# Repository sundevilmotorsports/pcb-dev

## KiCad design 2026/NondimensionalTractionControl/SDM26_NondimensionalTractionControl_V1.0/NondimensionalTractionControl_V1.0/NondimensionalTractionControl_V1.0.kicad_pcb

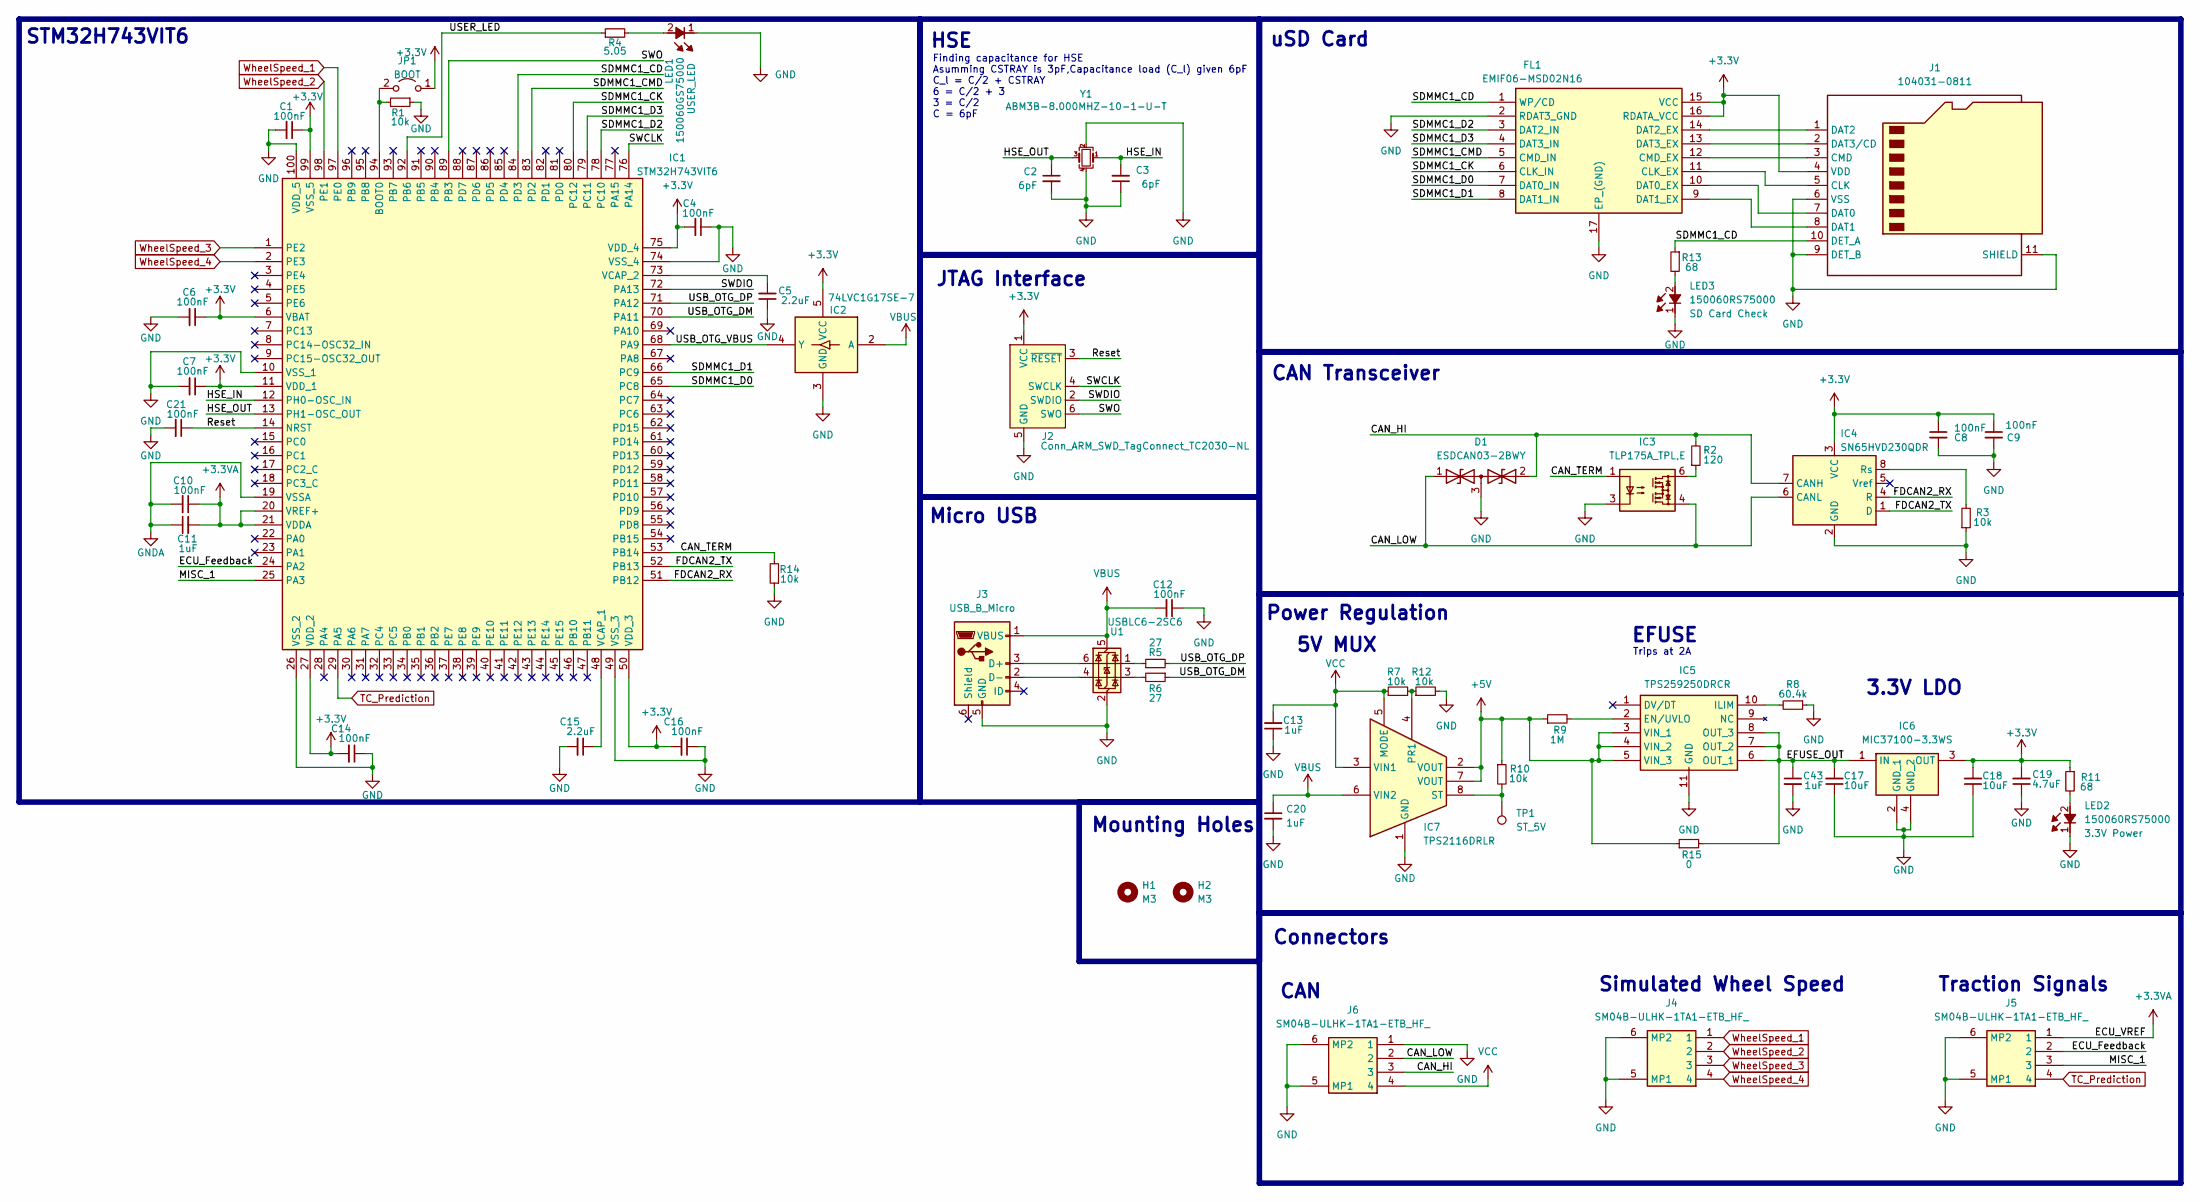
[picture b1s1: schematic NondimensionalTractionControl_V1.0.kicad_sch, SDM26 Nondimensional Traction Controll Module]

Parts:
C1, C4, C6, C7, C8, C9, C10, C12, C14, C16, C21: 100nF; C_0603_1608Metric
C2, C3: 6pF; C_0603_1608Metric
C5, C15: 2.2uF; C_0603_1608Metric
C11, C13, C20, C43: 1uF; C_0603_1608Metric
C17, C18: 10uF; C_0603_1608Metric
C19: 4.7uF; C_0603_1608Metric
D1: ESDCAN03-2BWY; SOT65P210X110-3N; Mouser Part Number 511-ESDCAN03-2BWY
FL1: EMIF06-MSD02N16; EMIF06MSD02N16; Mouser Part Number 511-EMIF06-MSD02N16
H1, H2: M3; MountingHole_3.2mm_M3
IC1: STM32H743VIT6; QFP50P1600X1600X160-100L; Mouser Part Number 511-STM32H743VIT6
IC2: 74LVC1G17SE-7; SOT65P210X110-5L; Mouser Part Number 621-74LVC1G17SE-7
IC3: TLP175A_TPL,E; TLP266J; Mouser Part Number 757-TLP175A(TPLE
IC4: SN65HVD230QDR; SOIC127P600X175-8L; Mouser Part Number 595-SN65HVD230QDR
IC5: TPS259250DRCR; SON50P300X300X100-11L-D; Mouser Part Number 595-TPS259250DRCR
IC6: MIC37100-3.3WS; SOT230P700X180-4N; Mouser Part Number 998-MIC37100-3.3WS
IC7: TPS2116DRLR; SOTFL50P160X60-8L; Mouser Part Number 595-TPS2116DRLR
J1: 104031-0811; 1040310811; Mouser Part Number 538-104031-0811
J2: Conn_ARM_SWD_TagConnect_TC2030-NL; Tag-Connect_TC2030-IDC-NL_2x03_P1.27mm_Vertical
J3: USB_B_Micro; USB_Micro-B_Molex-105017-0001
J4, J5, J6: SM04B-ULHK-1TA1-ETB_HF_; SM04BULHK1TA1ETBHF; Mouser Part Number 306-SM4BULH1TA1ETBHF
JP1: BOOT; PinHeader_1x02_P2.54mm_Vertical
LED1: 150060GS75000; LEDC1608X80N; Mouser Part Number 710-150060GS75000
LED2, LED3: 150060RS75000; LEDC1608X80N; Mouser Part Number 710-150060RS75000
R1, R3, R7, R10, R12, R14: 10k; R_0603_1608Metric
R2: 120; R_0603_1608Metric
R4: 5.05; R_0603_1608Metric
R5, R6: 27; R_0603_1608Metric
R8: 60.4k; R_0603_1608Metric
R9: 1M; R_0603_1608Metric
R11, R13: 68; R_0603_1608Metric
R15: 0; R_0603_1608Metric
TP1: ST_5V; TestPoint_Pad_1.5x1.5mm
U1: USBLC6-2SC6; SOT-23-6
Y1: ABM3B-8.000MHZ-10-1-U-T; ABM3B; Mouser Part Number 815-ABM3B8MHZ101UT

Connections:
+3.3V: C1.1, C4.2, C6.1, C7.1, C8.1, C9.1, C14.2, C16.2, C18.2, C19.2, FL1.15 (VCC), FL1.16 (RDATA_VCC), IC1.6 (VBAT), IC1.11 (VDD_1), IC1.27 (VDD_2), IC1.50 (VDD_3), IC1.75 (VDD_4), IC1.99 (VSS_5), IC2.5 (VCC), IC4.3 (VCC), IC6.3 (OUT), J1.4 (VDD), J2.1 (VCC), JP1.1 (A), R11.1
+3.3VA: C10.1, C11.2, IC1.20 (VREF+), IC1.21 (VDDA), J5.1
+5V: IC5.3 (VIN_1), IC5.4 (VIN_2), IC5.5 (VIN_3), IC7.2 (VOUT), IC7.7 (VOUT), R9.1, R10.1, R15.1
/CAN_HI: D1.2, IC4.7 (CANH), J6.3, R2.2
/CAN_LOW: D1.1, IC3.4, IC4.6 (CANL), J6.2
/CAN_TERM: IC1.53 (PB14), IC3.1, R14.2
/ECU_Feedback: IC1.24 (PA2), J5.2
/EFUSE_OUT: C17.2, C43.1, IC5.6 (OUT_1), IC5.7 (OUT_2), IC5.8 (OUT_3), IC6.1 (IN), R15.2
/FDCAN2_RX: IC1.51 (PB12), IC4.4 (R)
/FDCAN2_TX: IC1.52 (PB13), IC4.1 (D)
/HSE_IN: C3.2, IC1.12 (PH0-OSC_IN), Y1.1 (XTAL_1)
/HSE_OUT: C2.1, IC1.13 (PH1-OSC_OUT), Y1.3 (XTAL_2)
/MISC_1: IC1.25 (PA3), J5.3
/Reset: C21.1, IC1.14 (NRST), J2.3 (~RESET)
/SDMMC1_CD: FL1.1 (WP/CD), IC1.84 (PD3), J1.10 (DET_A), R13.1
/SDMMC1_CK: FL1.6 (CLK_IN), IC1.80 (PC12)
/SDMMC1_CMD: FL1.5 (CMD_IN), IC1.83 (PD2)
/SDMMC1_D0: FL1.7 (DAT0_IN), IC1.65 (PC8)
/SDMMC1_D1: FL1.8 (DAT1_IN), IC1.66 (PC9)
/SDMMC1_D2: FL1.3 (DAT2_IN), IC1.78 (PC10)
/SDMMC1_D3: FL1.4 (DAT3_IN), IC1.79 (PC11)
/SWCLK: IC1.76 (PA14), J2.4 (SWCLK)
/SWDIO: IC1.72 (PA13), J2.2 (SWDIO)
/SWO: IC1.89 (PB3), J2.6 (SWO)
/USB_OTG_DM: IC1.70 (PA11), R6.1
/USB_OTG_DP: IC1.71 (PA12), R5.2
/USB_OTG_VBUS: IC1.68 (PA9), IC2.4 (Y)
/USER_LED: IC1.92 (PB6), R4.1
GND: C1.2, C2.2, C3.1, C4.1, C5.1, C6.2, C7.2, C8.2, C9.2, C12.1, C13.1, C14.1, C15.2, C16.1, C17.1, C18.1, C19.1, C20.2, C21.2, C43.2, D1.3, FL1.2 (RDAT3_GND), FL1.17 (EP_(GND)), IC1.10 (VSS_1), IC1.26 (VSS_2), IC1.49 (VSS_3), IC1.74 (VSS_4), IC1.100 (VDD_5), IC2.3 (GND), IC3.3, IC4.2 (GND), IC5.11 (GND), IC6.2 (GND_1), IC6.4 (GND_2), IC7.1 (GND), J1.6 (VSS), J1.9 (DET_B), J1.11 (SHIELD), J2.5 (GND), J3.5 (GND), J4.5 (MP1), J4.6 (MP2), J5.5 (MP1), J5.6 (MP2), J6.1, J6.5 (MP1), J6.6 (MP2), LED1.1 (K), LED2.1 (K), LED3.1 (K), R1.1, R3.1, R8.1, R12.2, R14.1, U1.2 (GND), Y1.2 (GND_1), Y1.4 (GND_2)
GNDA: C10.2, C11.1, IC1.19 (VSSA)
unnamed: FL1.11 (CLK_EX), J1.5 (CLK)
unnamed: FL1.12 (CMD_EX), J1.3 (CMD)
unnamed: FL1.10 (DAT0_EX), J1.7 (DAT0)
unnamed: FL1.9 (DAT1_EX), J1.8 (DAT1)
unnamed: FL1.14 (DAT2_EX), J1.1 (DAT2)
unnamed: FL1.13 (DAT3_EX), J1.2 (DAT3/CD)
unnamed: IC1.94 (BOOT0), JP1.2 (B), R1.2
unnamed: C15.1, IC1.48 (VCAP_1)
unnamed: C5.2, IC1.73 (VCAP_2)
unnamed: IC3.6, R2.1
unnamed: IC4.8 (Rs), R3.2
unnamed: IC5.2 (EN/UVLO), R9.2
unnamed: IC5.10 (ILIM), R8.2
unnamed: IC7.4 (PR1), R7.2, R12.1
unnamed: IC7.8 (ST), R10.2, TP1.1
unnamed: J3.3 (D+), U1.6 (I/O1)
unnamed: J3.2 (D-), U1.4 (I/O2)
unnamed: LED1.2 (A), R4.2
unnamed: LED2.2 (A), R11.2
unnamed: LED3.2 (A), R13.2
unnamed: R5.1, U1.1 (I/O1)
unnamed: R6.2, U1.3 (I/O2)
TC_Prediction: IC1.29 (PA5), J5.4
VBUS: C12.2, C20.1, IC2.2 (A), IC7.6 (VIN2), J3.1 (VBUS), U1.5 (VBUS)
VCC: C13.2, IC7.3 (VIN1), IC7.5 (MODE), J6.4, R7.1
WheelSpeed_1: IC1.97 (PE0), J4.1
WheelSpeed_2: IC1.98 (PE1), J4.2
WheelSpeed_3: IC1.1 (PE2), J4.3
WheelSpeed_4: IC1.2 (PE3), J4.4

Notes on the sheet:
HSE
Power Regulation
Traction Signals
EFUSE
Mounting Holes
Simulated Wheel Speed
STM32H743VIT6
uSD Card
CAN
Trips at 2A
CAN Transceiver
JTAG Interface
3.3V LDO
5V MUX
Finding capacitance for HSE Asumming CSTRAY is 3pF,Capacitance load (C_l) given 6pF C_l = C/2 + CSTRAY 6 = C/2 + 3 3 = C/2 C = 6pF
Connectors
Micro USB

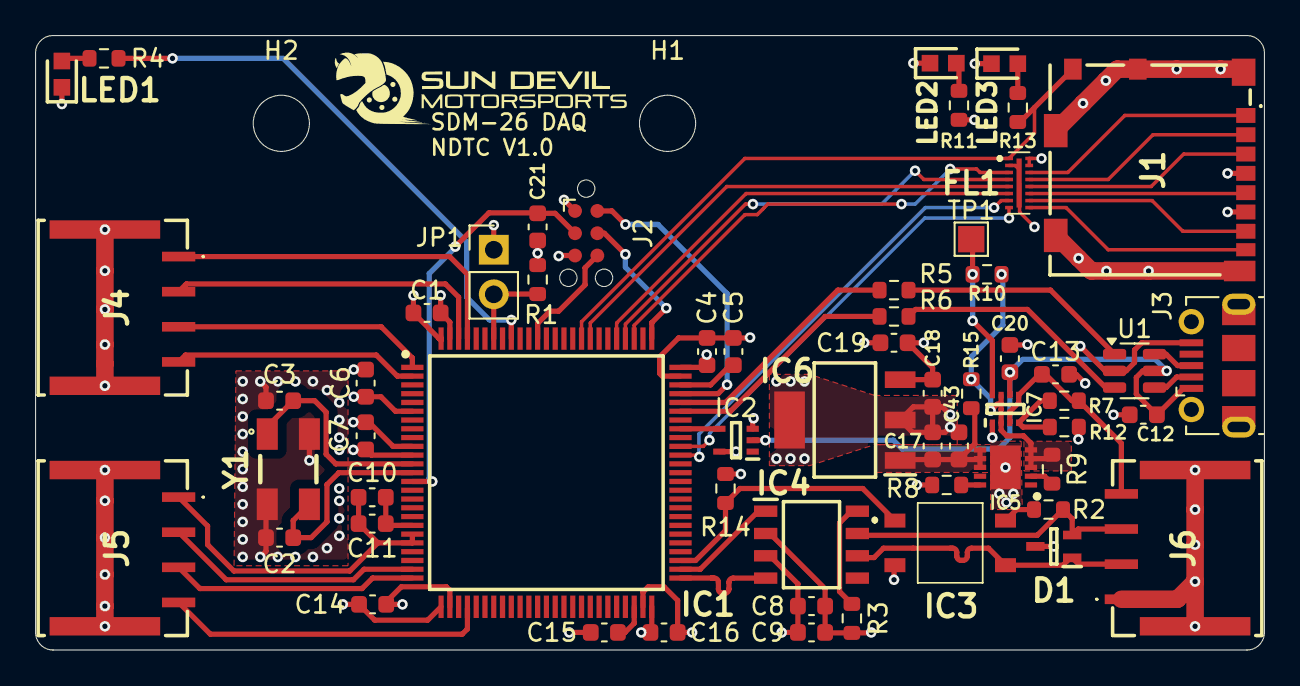
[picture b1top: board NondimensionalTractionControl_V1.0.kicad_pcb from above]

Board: 4 copper layers, 70.0 x 35.0 mm, 61 parts (0 on the bottom side), 59 nets.

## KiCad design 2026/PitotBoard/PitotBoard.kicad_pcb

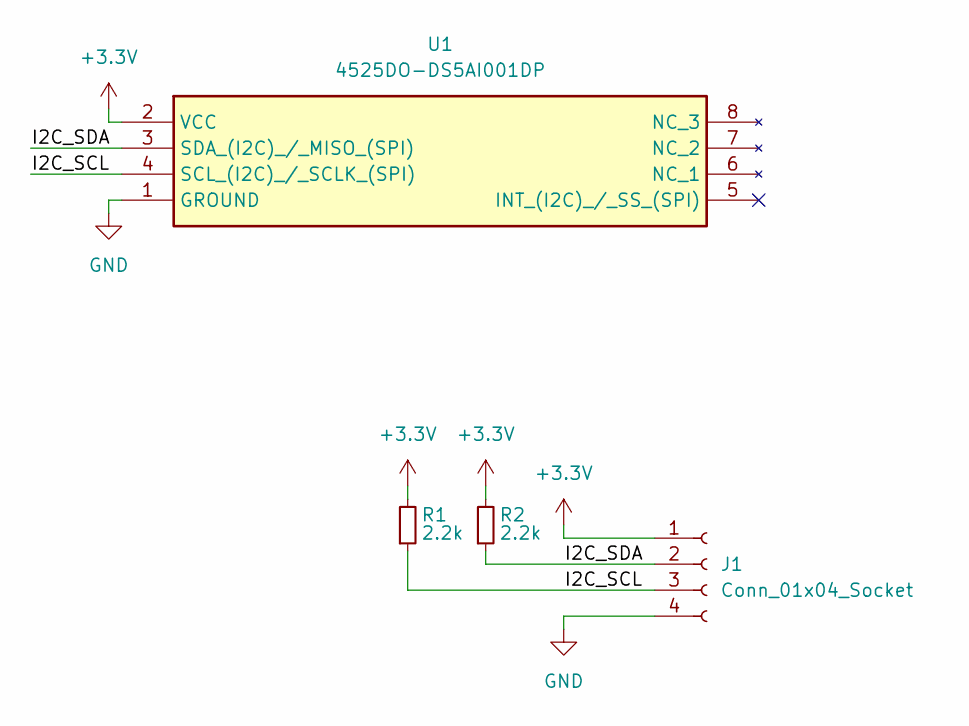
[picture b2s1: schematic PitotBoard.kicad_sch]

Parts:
J1: Conn_01x04_Socket; JST_XH_B4B-XH-A_1x04_P2.50mm_Vertical
R1, R2: 2.2k; R_0603_1608Metric
U1: 4525DO-DS5AI001DP; 4525DO-DS...P; Mouser Part Number 824-4525DODS5AI001DP

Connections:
+3.3V: J1.1, R1.2, R2.2, U1.2 (VCC)
/I2C_SCL: J1.3, R1.1, U1.4 (SCL_(I2C)_/_SCLK_(SPI))
/I2C_SDA: J1.2, R2.1, U1.3 (SDA_(I2C)_/_MISO_(SPI))
GND: J1.4, U1.1 (GROUND)

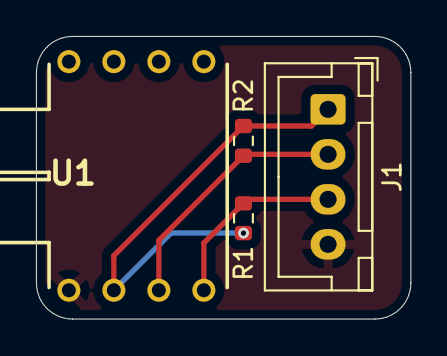
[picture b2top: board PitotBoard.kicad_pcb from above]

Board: 2 copper layers, 20.8 x 15.7 mm, 4 parts (0 on the bottom side), 4 nets.

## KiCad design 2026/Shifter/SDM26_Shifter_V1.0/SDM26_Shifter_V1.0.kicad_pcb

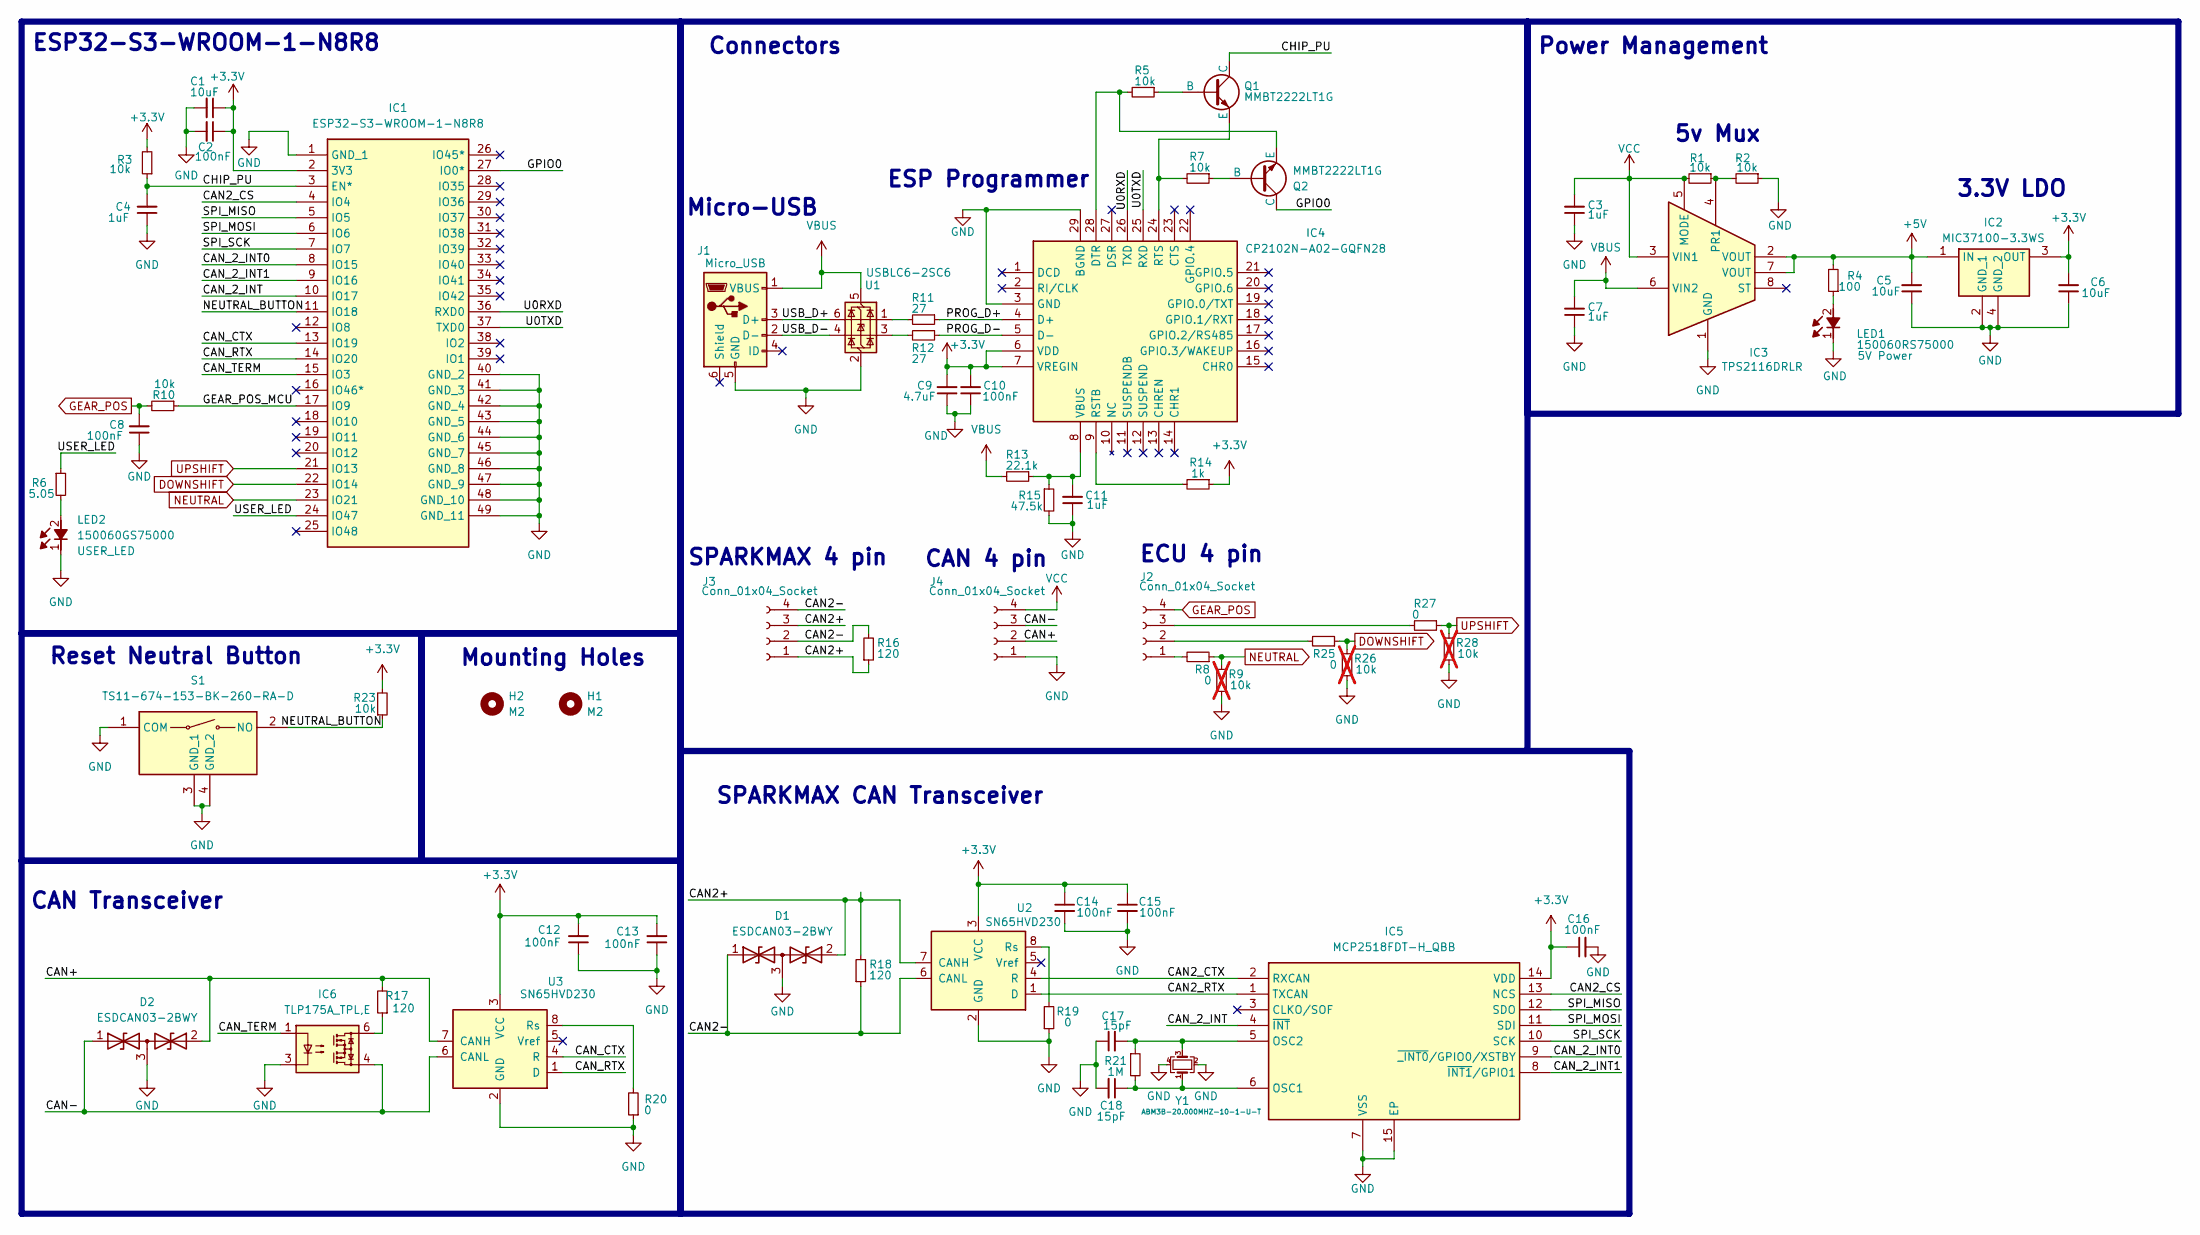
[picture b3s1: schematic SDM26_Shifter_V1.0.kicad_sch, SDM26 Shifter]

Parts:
C1, C5, C6: 10uF; C_0603_1608Metric
C2, C8, C10, C12, C13, C14, C15, C16: 100nF; C_0603_1608Metric
C3, C4, C7, C11: 1uF; C_0603_1608Metric
C9: 4.7uF; C_0603_1608Metric
C17, C18: 15pF; C_0603_1608Metric
D1, D2: ESDCAN03-2BWY; SOT65P210X110-3N; Mouser Part Number 511-ESDCAN03-2BWY
H1, H2: M2; MountingHole_2.2mm_M2
IC1: ESP32-S3-WROOM-1-N8R8; ESP32S3WROOM1N8R8; Mouser Part Number 356-EP32S3WROOM1N8R8
IC2: MIC37100-3.3WS; SOT230P700X180-4N; Mouser Part Number 998-MIC37100-3.3WS
IC3: TPS2116DRLR; SOTFL50P160X60-8L; Mouser Part Number 595-TPS2116DRLR
IC4: CP2102N-A02-GQFN28; QFN50P500X500X80-29N-D; Mouser Part Number 634-CP2102NA02GQFN28
IC5: MCP2518FDT-H_QBB; SON65P300X450X90-15L-D; Mouser Part Number 579-MCP2518FDT-H/QBB
IC6: TLP175A_TPL,E; TLP266J; Mouser Part Number 757-TLP175A(TPLE
J1: Micro_USB; USB_Micro-B_Molex-105017-0001
J2, J3, J4: Conn_01x04_Socket; JST_EH_S4B-EH_1x04_P2.50mm_Horizontal_1
LED1: 150060RS75000; LEDC1608X80N; Mouser Part Number 710-150060RS75000
LED2: 150060GS75000; LEDC1608X80N; Mouser Part Number 710-150060VS75000
Q1, Q2: MMBT2222LT1G; SOT96P237X111-3N
R1, R2, R3, R5, R7, R10, R23: 10k; R_0603_1608Metric
R4: 100; R_0603_1608Metric
R6: 5.05; R_0603_1608Metric
R8, R19, R20, R25, R27: 0; R_0603_1608Metric
R9, R26, R28: 10k; R_0603_1608Metric; not fitted
R11, R12: 27; R_0603_1608Metric
R13: 22.1k; R_0603_1608Metric
R14: 1k; R_0603_1608Metric
R15: 47.5k; R_0603_1608Metric
R16, R17, R18: 120; R_0603_1608Metric
R21: 1M; R_0603_1608Metric
S1: TS11-674-153-BK-260-RA-D; TS1167473BK260RAD; Mouser Part Number 179-TS1167473260RAD
U1: USBLC6-2SC6; SOT-23-6
U2, U3: SN65HVD230; SOIC-8_3.9x4.9mm_P1.27mm
Y1: ABM3B-20.000MHZ-10-1-U-T; ABM3B; Mouser Part Number 815-ABM3B-20-T

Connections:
+3.3V: C1.1, C2.1, C6.2, C9.2, C10.2, C12.2, C13.2, C14.1, C15.1, C16.1, IC1.2 (3V3), IC2.3 (OUT), IC4.6 (VDD), IC4.7 (VREGIN), IC5.14 (VDD), R3.2, R14.1, R23.2, U2.3 (VCC), U3.3 (VCC)
+5V: C5.2, IC2.1 (IN), IC3.2 (VOUT), IC3.7 (VOUT), R4.2
/CAN2+: D1.2, J3.1, J3.3, R16.1, R18.2, U2.7 (CANH)
/CAN2-: D1.1, J3.2, J3.4, R16.2, R18.1, U2.6 (CANL)
/CAN2_CS: IC1.4 (IO4), IC5.13 (NCS)
/CAN2_CTX: IC5.2 (RXCAN), U2.4 (R)
/CAN2_RTX: IC5.1 (TXCAN), U2.1 (D)
/CAN+: D2.2, J4.2, R17.2, U3.7 (CANH)
/CAN-: D2.1, IC6.4, J4.3, U3.6 (CANL)
/CAN_2_INT: IC1.10 (IO17), IC5.4 (~INT)
/CAN_2_INT0: IC1.8 (IO15), IC5.9 (~_INT0/GPIO0/XSTBY)
/CAN_2_INT1: IC1.9 (IO16), IC5.8 (~INT1/GPIO1)
/CAN_CTX: IC1.13 (IO19), U3.4 (R)
/CAN_RTX: IC1.14 (IO20), U3.1 (D)
/CAN_TERM: IC1.15 (IO3), IC6.1
/CHIP_PU: C4.2, IC1.3 (EN*), Q1.3 (C), R3.1
/GEAR_POS_MCU: IC1.17 (IO9), R10.1
/GPIO0: IC1.27 (IO0*), Q2.3 (C)
/NEUTRAL_BUTTON: IC1.11 (IO18), R23.1, S1.2 (NO)
/PROG_D+: IC4.4 (D+), R11.1
/PROG_D-: IC4.5 (D-), R12.1
/SPI_MISO: IC1.5 (IO5), IC5.12 (SDO)
/SPI_MOSI: IC1.6 (IO6), IC5.11 (SDI)
/SPI_SCK: IC1.7 (IO7), IC5.10 (SCK)
/U0RXD: IC1.36 (RXD0), IC4.26 (TXD)
/U0TXD: IC1.37 (TXD0), IC4.25 (RXD)
/USB_D+: J1.3 (D+), U1.6 (I/O1)
/USB_D-: J1.2 (D-), U1.4 (I/O2)
/USER_LED: IC1.24 (IO47), R6.1
DOWNSHIFT: IC1.22 (IO14), R25.1, R26.1
GEAR_POS: C8.2, J2.4, R10.2
GND: C1.2, C2.2, C3.1, C4.1, C5.1, C6.1, C7.1, C8.1, C9.1, C10.1, C11.1, C12.1, C13.1, C14.2, C15.2, C16.2, C17.1, C18.2, D1.3, D2.3, IC1.1 (GND_1), IC1.40 (GND_2), IC1.41 (GND_3), IC1.42 (GND_4), IC1.43 (GND_5), IC1.44 (GND_6), IC1.45 (GND_7), IC1.46 (GND_8), IC1.47 (GND_9), IC1.48 (GND_10), IC1.49 (GND_11), IC2.2 (GND_1), IC2.4 (GND_2), IC3.1 (GND), IC4.3 (GND), IC4.29 (BGND), IC5.7 (VSS), IC5.15 (EP), IC6.3, J1.5 (GND), J4.1, LED1.1 (K), LED2.1 (K), R2.1, R9.2, R15.2, R19.1, R20.1, R26.2, R28.2, S1.1 (COM), S1.3 (GND_1), S1.4 (GND_2), U1.2 (GND), U2.2 (GND), U3.2 (GND), Y1.2 (GND_1), Y1.4 (GND_2)
NEUTRAL: IC1.23 (IO21), R8.1, R9.1
unnamed: IC3.4 (PR1), R1.1, R2.2
unnamed: IC4.28 (DTR), Q2.2 (E), R5.2
unnamed: IC4.9 (RSTB), R14.2
unnamed: IC4.24 (RTS), Q1.2 (E), R7.2
unnamed: C11.2, IC4.8 (VBUS), R13.1, R15.1
unnamed: C18.1, IC5.6 (OSC1), R21.2, Y1.1 (XTAL_1)
unnamed: C17.2, IC5.5 (OSC2), R21.1, Y1.3 (XTAL_2)
unnamed: IC6.6, R17.1
unnamed: J2.1, R8.2
unnamed: J2.2, R25.2
unnamed: J2.3, R27.2
unnamed: LED1.2 (A), R4.1
unnamed: LED2.2 (A), R6.2
unnamed: Q1.1 (B), R5.1
unnamed: Q2.1 (B), R7.1
unnamed: R11.2, U1.1 (I/O1)
unnamed: R12.2, U1.3 (I/O2)
unnamed: R19.2, U2.8 (Rs)
unnamed: R20.2, U3.8 (Rs)
UPSHIFT: IC1.21 (IO13), R27.1, R28.1
VBUS: C7.2, IC3.6 (VIN2), J1.1 (VBUS), R13.2, U1.5 (VBUS)
VCC: C3.2, IC3.3 (VIN1), IC3.5 (MODE), J4.4, R1.2

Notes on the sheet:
SPARKMAX CAN Transceiver
CAN 4 pin
Connectors
Reset Neutral Button
Micro-USB
CAN Transceiver
3.3V LDO
ESP32-S3-WROOM-1-N8R8
ESP Programmer
Power Management
5v Mux
SPARKMAX 4 pin
Mounting Holes
ECU 4 pin

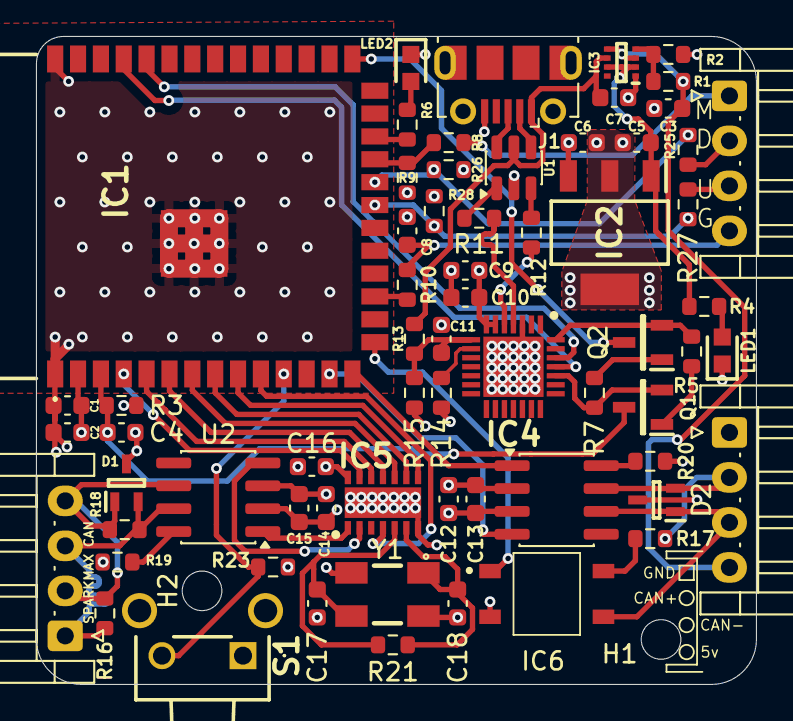
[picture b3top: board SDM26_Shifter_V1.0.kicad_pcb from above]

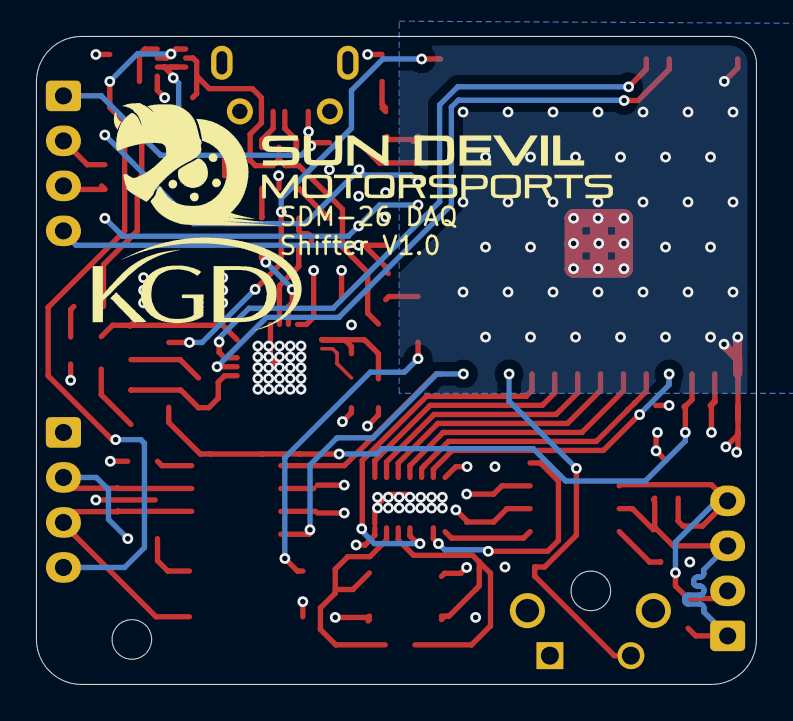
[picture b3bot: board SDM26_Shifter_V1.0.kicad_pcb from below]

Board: 4 copper layers, 40.0 x 36.0 mm, 67 parts (2 on the bottom side), 55 nets.

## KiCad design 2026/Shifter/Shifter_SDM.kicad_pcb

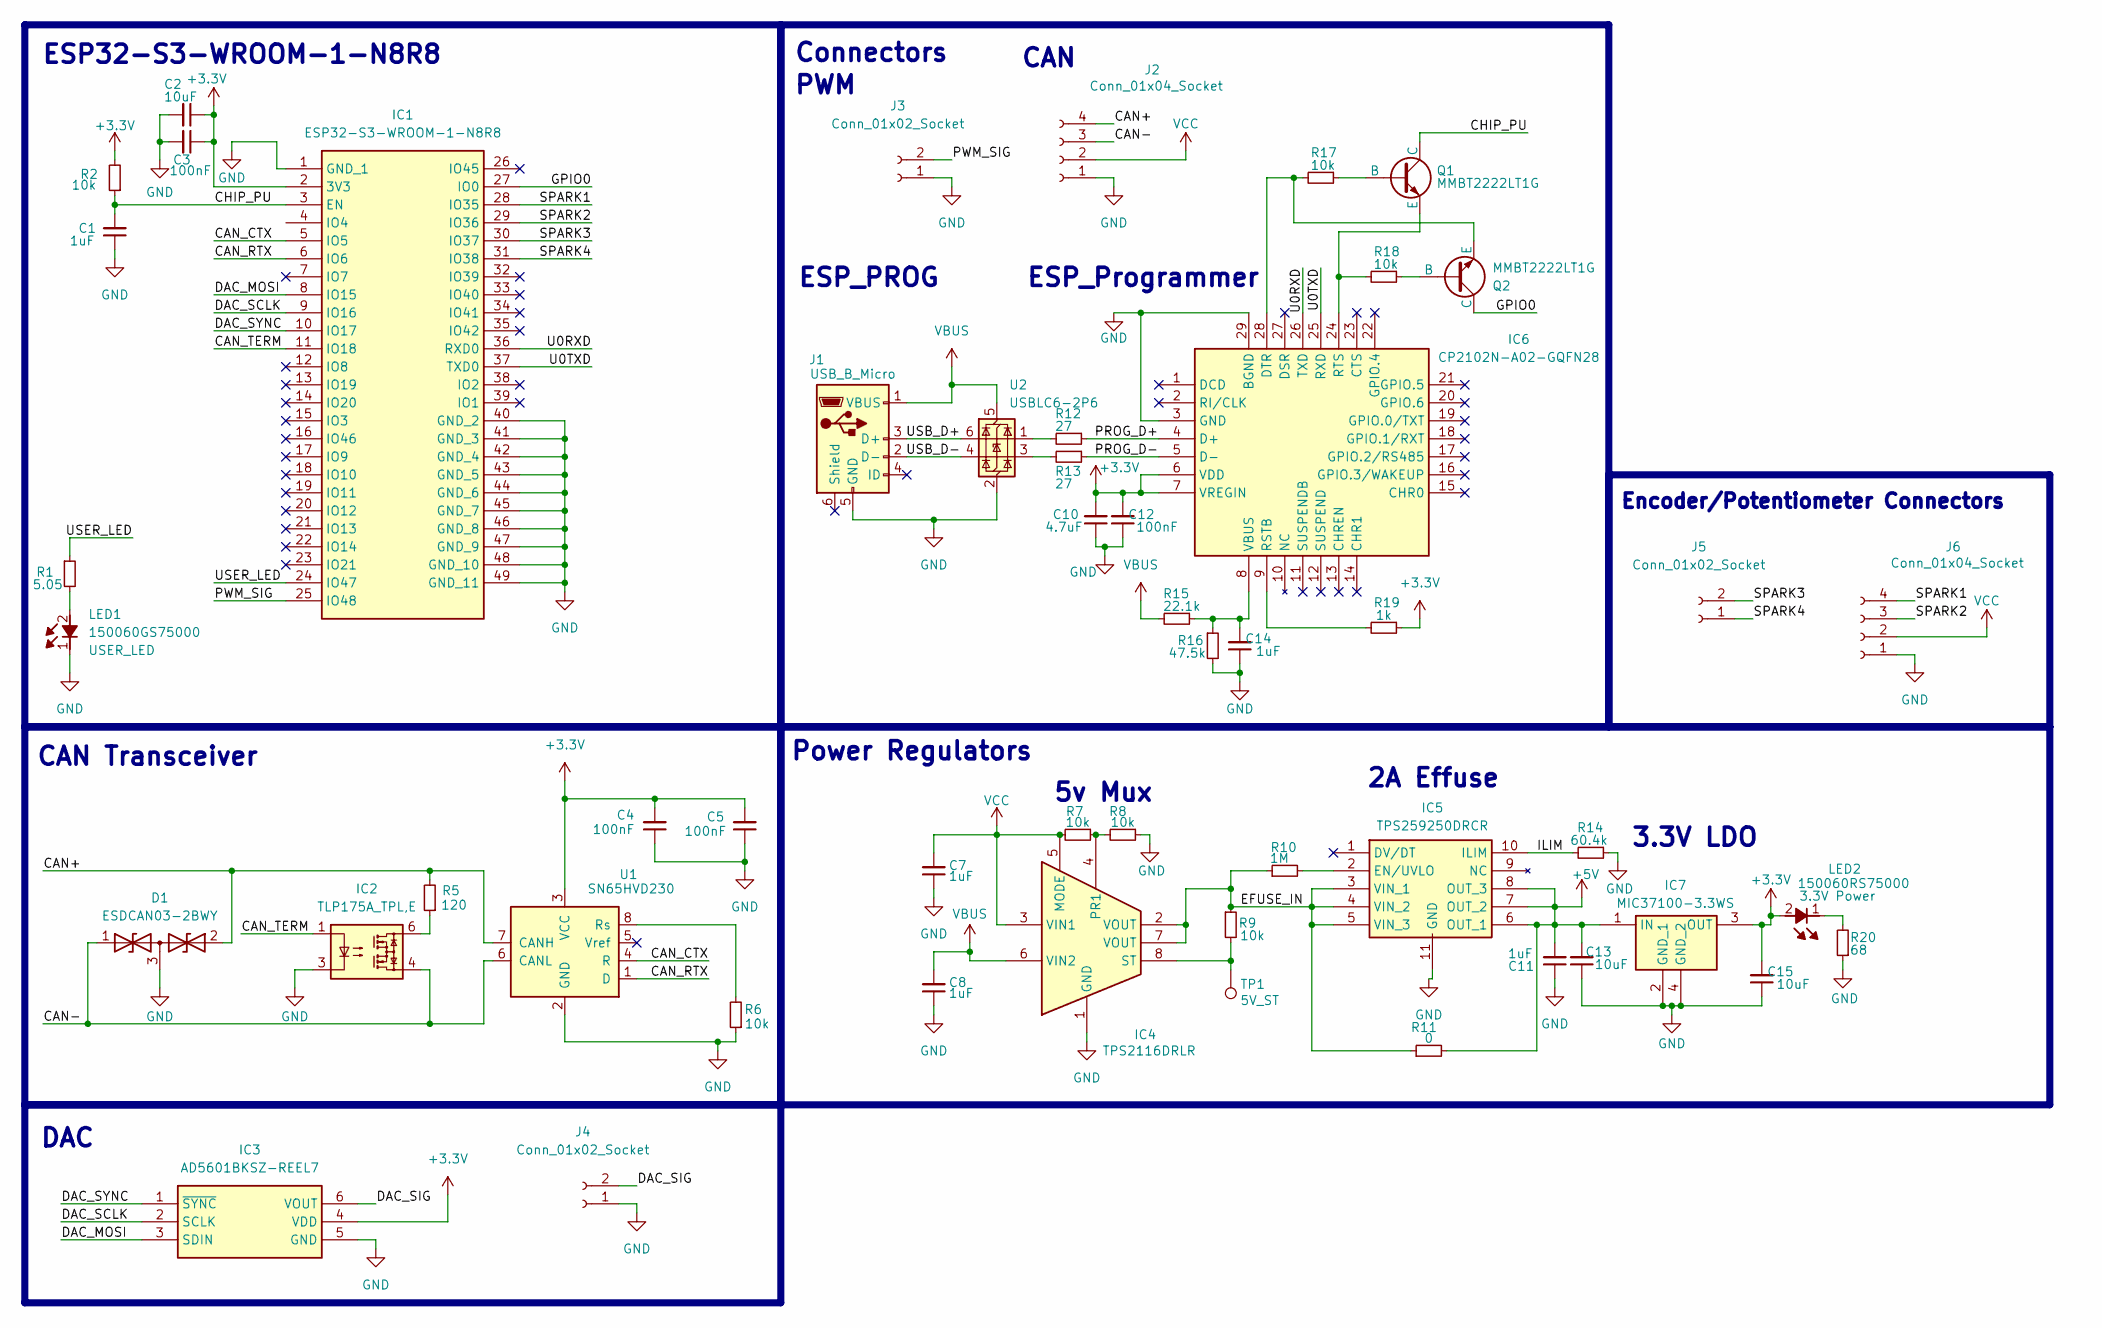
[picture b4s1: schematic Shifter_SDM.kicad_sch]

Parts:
C1, C7, C8, C11, C14: 1uF; C_0603_1608Metric
C2, C13, C15: 10uF; C_0603_1608Metric
C3, C4, C5, C12: 100nF; C_0603_1608Metric
C10: 4.7uF; C_0603_1608Metric
D1: ESDCAN03-2BWY; SOT65P210X110-3N; Mouser Part Number 511-ESDCAN03-2BWY
IC1: ESP32-S3-WROOM-1-N8R8; ESP32S3WROOM1N8R8; Mouser Part Number 356-EP32S3WROOM1N8R8
IC2: TLP175A_TPL,E; TLP266J; Mouser Part Number 757-TLP175A(TPLE
IC3: AD5601BKSZ-REEL7; SOT65P210X100-6N; Mouser Part Number 584-AD5601BKSZ-R7
IC4: TPS2116DRLR; SOTFL50P160X60-8L; Mouser Part Number 595-TPS2116DRLR
IC5: TPS259250DRCR; SON50P300X300X100-11L-D; Mouser Part Number 595-TPS259250DRCR
IC6: CP2102N-A02-GQFN28; QFN50P500X500X80-29N-D; Mouser Part Number 634-CP2102NA02GQFN28
IC7: MIC37100-3.3WS; SOT230P700X180-4N; Mouser Part Number 998-MIC37100-3.3WS
J1: USB_B_Micro; USB_Micro-B_Molex-105017-0001
J2, J6: Conn_01x04_Socket; JST_XH_S4B-XH-A_1x04_P2.50mm_Horizontal
J3, J4, J5: Conn_01x02_Socket; JST_EH_S2B-EH_1x02_P2.50mm_Horizontal
LED1: 150060GS75000; LED_0603_1608Metric; Mouser Part Number 710-150060VS75000
LED2: 150060RS75000; LED_0603_1608Metric; Mouser Part Number 710-150060RS75000
Q1, Q2: MMBT2222LT1G; SOT96P237X111-3N
R1: 5.05; R_0603_1608Metric
R2, R6, R7, R8, R9, R17, R18: 10k; R_0603_1608Metric
R5: 120; R_0603_1608Metric
R10: 1M; R_0603_1608Metric
R11: 0; R_0603_1608Metric
R12, R13: 27; R_0603_1608Metric
R14: 60.4k; R_0603_1608Metric
R15: 22.1k; R_0603_1608Metric
R16: 47.5k; R_0603_1608Metric
R19: 1k; R_0603_1608Metric
R20: 68; R_0603_1608Metric
TP1: 5V_ST; TestPoint_Pad_1.5x1.5mm
U1: SN65HVD230; SOIC-8_3.9x4.9mm_P1.27mm
U2: USBLC6-2P6; SOT-23-6

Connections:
+3.3V: C2.1, C3.1, C4.2, C5.2, C10.2, C12.2, C15.2, IC1.2 (3V3), IC3.4 (VDD), IC6.6 (VDD), IC6.7 (VREGIN), IC7.3 (OUT), LED2.2 (A), R2.2, R19.1, U1.3 (VCC)
+5V: C11.2, C13.2, IC5.6 (OUT_1), IC5.7 (OUT_2), IC5.8 (OUT_3), IC7.1 (IN), R11.2
/CAN+: D1.2, J2.4, R5.2, U1.7 (CANH)
/CAN-: D1.1, IC2.4, J2.3, U1.6 (CANL)
/CAN_CTX: IC1.5 (IO5), U1.4 (R)
/CAN_RTX: IC1.6 (IO6), U1.1 (D)
/CAN_TERM: IC1.11 (IO18), IC2.1
/CHIP_PU: C1.2, IC1.3 (EN), Q1.3 (C), R2.1
/DAC_MOSI: IC1.8 (IO15), IC3.3 (SDIN)
/DAC_SCLK: IC1.9 (IO16), IC3.2 (SCLK)
/DAC_SIG: IC3.6 (VOUT), J4.2
/DAC_SYNC: IC1.10 (IO17), IC3.1 (~SYNC)
/EFUSE_IN: IC4.2 (VOUT), IC4.7 (VOUT), IC5.3 (VIN_1), IC5.4 (VIN_2), IC5.5 (VIN_3), R9.1, R10.1, R11.1
/GPIO0: IC1.27 (IO0), Q2.3 (C)
/ILIM: IC5.10 (ILIM), R14.2
/PROG_D+: IC6.4 (D+), R12.1
/PROG_D-: IC6.5 (D-), R13.1
/PWM_SIG: IC1.25 (IO48), J3.2
/SPARK1: IC1.28 (IO35), J6.4
/SPARK2: IC1.29 (IO36), J6.3
/SPARK3: IC1.30 (IO37), J5.2
/SPARK4: IC1.31 (IO38), J5.1
/U0RXD: IC1.36 (RXD0), IC6.26 (TXD)
/U0TXD: IC1.37 (TXD0), IC6.25 (RXD)
/USB_D+: J1.3 (D+), U2.6 (I/O1)
/USB_D-: J1.2 (D-), U2.4 (I/O2)
/USER_LED: IC1.24 (IO47), R1.1
GND: C1.1, C2.2, C3.2, C4.1, C5.1, C7.1, C8.1, C10.1, C11.1, C12.1, C13.1, C14.1, C15.1, D1.3, IC1.1 (GND_1), IC1.40 (GND_2), IC1.41 (GND_3), IC1.42 (GND_4), IC1.43 (GND_5), IC1.44 (GND_6), IC1.45 (GND_7), IC1.46 (GND_8), IC1.47 (GND_9), IC1.48 (GND_10), IC1.49 (GND_11), IC2.3, IC3.5 (GND), IC4.1 (GND), IC5.11 (GND), IC6.3 (GND), IC6.29 (BGND), IC7.2 (GND_1), IC7.4 (GND_2), J1.5 (GND), J2.1, J3.1, J4.1, J6.1, LED1.1 (K), R6.1, R8.1, R14.1, R16.2, R20.1, U1.2 (GND), U2.2 (GND)
unnamed: IC2.6, R5.1
unnamed: IC4.4 (PR1), R7.1, R8.2
unnamed: IC4.8 (ST), R9.2, TP1.1
unnamed: IC5.2 (EN/UVLO), R10.2
unnamed: IC6.28 (DTR), Q2.2 (E), R17.2
unnamed: IC6.9 (RSTB), R19.2
unnamed: IC6.24 (RTS), Q1.2 (E), R18.2
unnamed: C14.2, IC6.8 (VBUS), R15.1, R16.1
unnamed: LED1.2 (A), R1.2
unnamed: LED2.1 (K), R20.2
unnamed: Q1.1 (B), R17.1
unnamed: Q2.1 (B), R18.1
unnamed: R12.2, U2.1 (I/O1)
unnamed: R13.2, U2.3 (I/O2)
unnamed: R6.2, U1.8 (Rs)
VBUS: C8.2, IC4.6 (VIN2), J1.1 (VBUS), R15.2, U2.5 (VBUS)
VCC: C7.2, IC4.3 (VIN1), IC4.5 (MODE), J2.2, J6.2, R7.2

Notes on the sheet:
ESP_Programmer
CAN
Power Regulators
3.3V LDO
Encoder/Potentiometer Connectors
5v Mux
Connectors
PWM
ESP32-S3-WROOM-1-N8R8
ESP_PROG
2A Effuse
DAC
CAN Transceiver

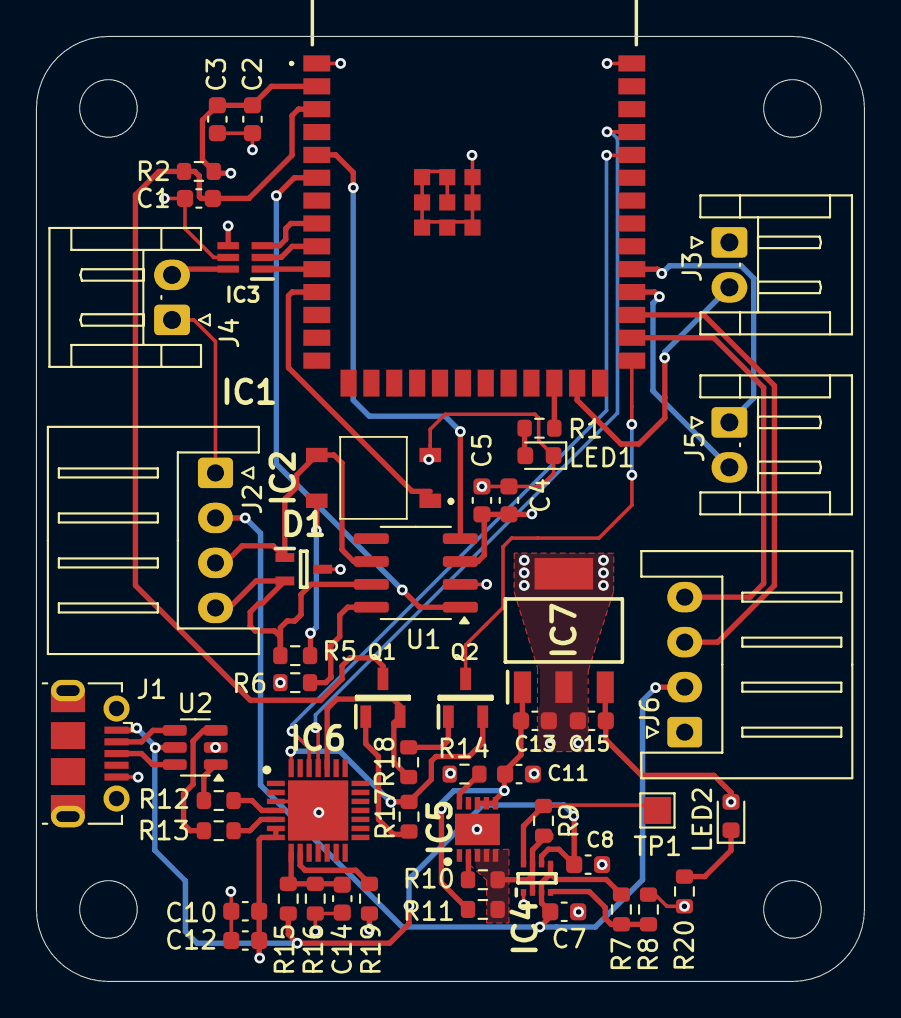
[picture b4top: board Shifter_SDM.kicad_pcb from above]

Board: 4 copper layers, 46.0 x 52.5 mm, 52 parts (0 on the bottom side), 45 nets.
